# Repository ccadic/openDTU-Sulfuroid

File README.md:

# openDTU-Sulfuroid

Derived from :https://www.opendtu.solar/ 
The pcb is for sale on : https://www.tindie.com/products/electronictrik/esp32s3-opendtu-solar-monitoring-tool/

**Introducing the revolutionary OpenDTU Module: The Future of Solar Energy Management!**

In a world where sustainable energy is not just an option but a necessity, the OpenDTU Module stands as a beacon of innovation and efficiency. Designed with precision and crafted for excellence, this cutting-edge Printed Circuit Board (PCB) is your ultimate gateway to optimizing solar energy production.

The OpenDTU Module revolutionizes the way we interact with solar micro-inverters. Its state-of-the-art design allows for seamless querying of solar micro-inverters, providing you with real-time insights into your energy production. This isn't just about monitoring; it's about maximizing efficiency, reducing costs, and stepping into a future where your solar energy system is smarter and more responsive than ever before.

**Key Features:**

- **Real-Time Monitoring**: Instant access to your energy production data. Watch your energy yield as it happens and make informed decisions on the fly.
- **Universal Compatibility**: Designed to communicate effortlessly with a wide range of solar micro-inverters. The OpenDTU Module speaks the language of your devices.
- **Advanced Analytics**: Not just numbers, but insights. Understand your energy patterns, predict future production, and identify areas for improvement.
- **User-Friendly Interface**: Whether you're a tech wizard or a beginner, the OpenDTU Module offers a simple, intuitive interface for everyone.
- **Robust Design**: Built to last. With its durable components and meticulous design, the OpenDTU Module withstands the test of time and weather.
- **Open Source Freedom**: Unleash the power of community-driven innovation. Customize, enhance, and share your improvements with an ever-growing network of users and developers.
- **Eco-Friendly Operation**: Embrace sustainability not just in energy production but in management too. The OpenDTU Module is designed with eco-conscious materials and processes.

Imagine a world where your solar energy system is not just a part of your home, but a smart, interactive partner in your quest for a sustainable future. The OpenDTU Module brings that world to your doorstep.

Perfect for homeowners, businesses, and solar enthusiasts alike, the OpenDTU Module is more than a PCB; it's a commitment to a brighter, greener planet. Embrace the future of solar energy management today and transform the way you power your world.

Welcome to the era of intelligent solar energy. Welcome to the OpenDTU Module.

Config File for the openDTU PCB

Radio modules: https://www.amazon.fr/gp/product/B07VQ838KT/ref=ppx_yo_dt_b_asin_title_o02_s00?ie=UTF8&psc=1
ESP31S3 Long Sev board: https://fr.aliexpress.com/item/1005004642646719.html
Display: https://www.aliexpress.com/item/1005005921902141.html

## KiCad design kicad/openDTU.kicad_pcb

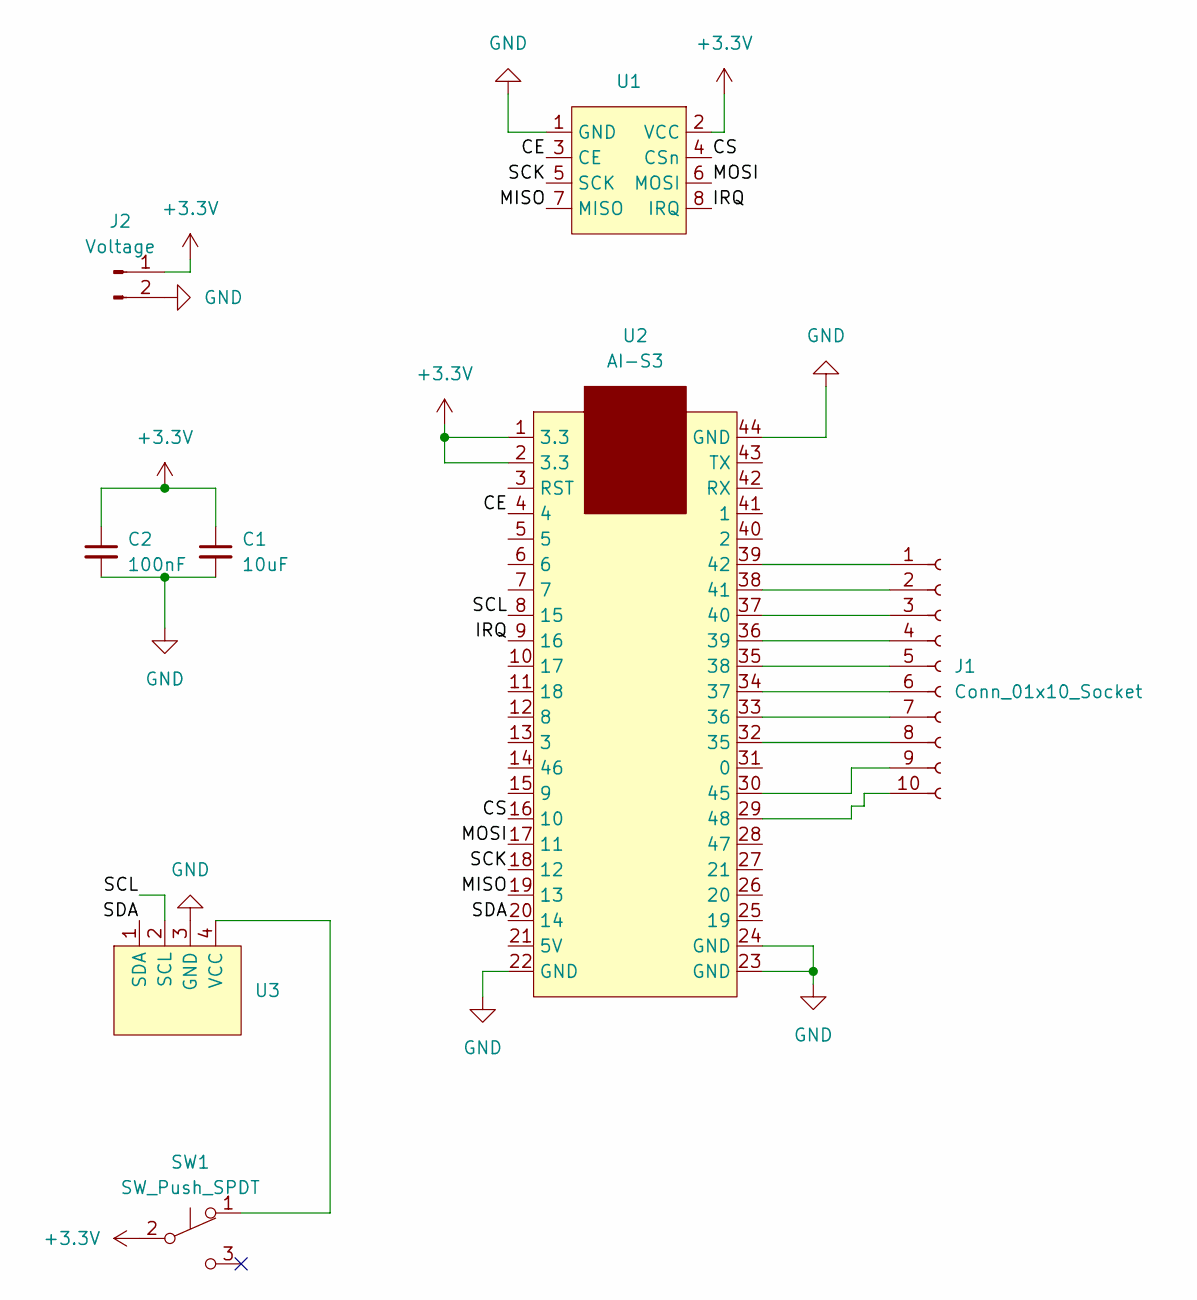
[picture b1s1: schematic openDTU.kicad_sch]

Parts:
C1: 10uF; C_0603_1608Metric
C2: 100nF; C_0603_1608Metric
J1: Conn_01x10_Socket; PinHeader_1x10_P2.54mm_Vertical
J2: Voltage; 2padsfree
SW1: SW_Push_SPDT; SW_SPDT_PCM12
U1: NRF24l01
U2: AI-S3
U3: GM12864-59N

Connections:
+3.3V: C1.1, C2.1, J2.1, SW1.2 (B), U1.2 (VCC), U2.1 (3.3), U2.2 (3.3)
/CE: U1.3 (CE), U2.4
/CS: U1.4 (CSn), U2.16 (10)
/IRQ: U1.8 (IRQ), U2.9 (16)
/MISO: U1.7 (MISO), U2.19 (13)
/MOSI: U1.6 (MOSI), U2.17 (11)
/SCK: U1.5 (SCK), U2.18 (12)
/SCL: U2.8 (15), U3.2 (SCL)
/SDA: U2.20 (14), U3.1 (SDA)
GND: C1.2, C2.2, J2.2, U1.1 (GND), U2.22 (GND), U2.23 (GND), U2.24 (GND), U2.44 (GND), U3.3 (GND)
unnamed: J1.1, U2.39 (42)
unnamed: J1.2, U2.38 (41)
unnamed: J1.3, U2.37 (40)
unnamed: J1.4, U2.36 (39)
unnamed: J1.5, U2.35 (38)
unnamed: J1.6, U2.34 (37)
unnamed: J1.7, U2.33 (36)
unnamed: J1.8, U2.32 (35)
unnamed: J1.9, U2.30 (45)
unnamed: J1.10, U2.29 (48)
unnamed: SW1.1 (A), U3.4 (VCC)

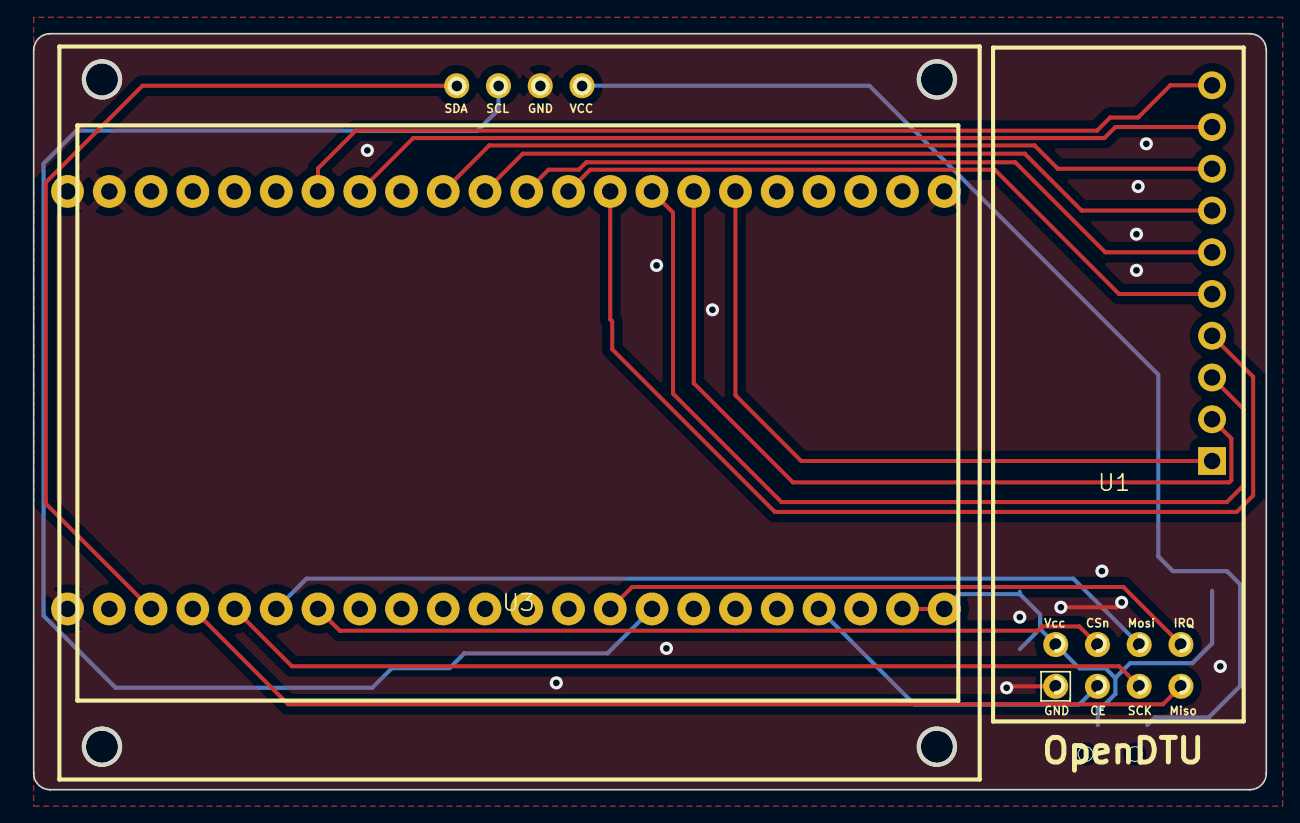
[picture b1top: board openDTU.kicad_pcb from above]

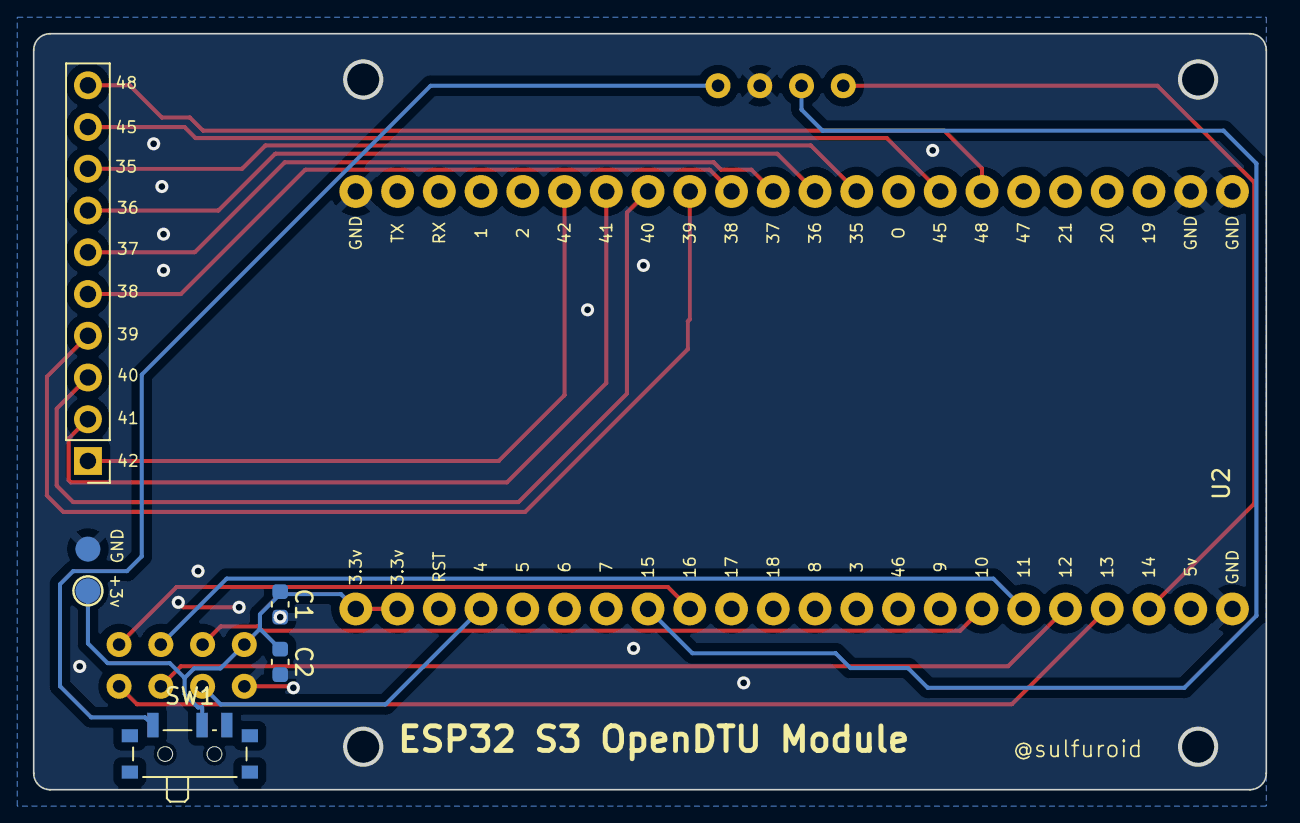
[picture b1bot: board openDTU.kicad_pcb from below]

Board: 2 copper layers, 74.9 x 45.8 mm, 8 parts (6 on the bottom side), 21 nets.
